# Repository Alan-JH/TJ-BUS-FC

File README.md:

# Piridium Hardware
Piridium is a CubeSat bus design inspired by TJREVERB and the concept of Pycubed. It uses a Raspberry Pi Zero as a flight computer and Iridium 9602N modem as a radio. The bus is divided into two boards, with the EPS board including six 18650 battery cells and protection and balancing circuitry, and the avionics board including everything else (flight computer, radio, telemetry ADC, inhibits and RBF, solar input charge regulators, 5V output regulator, inertial measurement unit, real time clock and CR2032 battery backup, and payload connector).

## Issues
Charge balance for current EPS prototype seems to not work, despite following datasheet recommendations exactly. Possibly a bad chip, but worth noting.

## Tech Specs
Flight Computer: Raspberry Pi Zero/Zero W

Radio: Iridium 9602N Short Burst Data

Clock: DS3232M RTC with CR2032 Battery Backup

Battery: Six 18650 Li-Ion cells (builder's discretion, recommend protected 3-4Ah) in a 3P2S configuration

Battery protection: ~7.7A overcurrent protection (charge & discharge), 4.29V/cell overcharge protection with hysteresis down to 4.05V/cell, 3V/cell overdischarge protection with hysteresis up to 3.2V/cell

Solar input: 4 input connectors feeding two regulators with 25V Max (limited by the voltage divider for telemetry) with charge cutoff at 8.27V, MPPT settable using a trim pot

Output regulation: 2 separated 5V rails up to 3A output, one for the radio, the other for the Raspberry Pi, each with latching current limiters and a watchdog timer

Payload connection: 1x SPI bus with one dedicated chip enable pin, 1x I2C bus, 1x unused configurable GPIO pin, switchable battery power (no overcurrent protection); see schematic for pinout

Telemetry: Current out and voltage in for both solar regulators, battery input voltage and current, payload battery current

Antenna connector: Standard SMA vertical

Inhibits: Two discharge inhibits (do not block charge), two RBF (one low side ground disconnect, one high side power disconnect, blocks both charge and discharge)

## Hardware notes

### Flight Computer
Raspberry Pi Zero running Raspbian OS lite. Flight software can be found here: https://github.com/Alan-JH/piridium-fsw

### Iridium Modem
Defaults to off when the bus is powered, only turns on when S_MODEM_ON_OFF is pulled high by the Raspberry Pi on GPIO pin 20. There is an LED to indicate when the modem is powered, and GPIO input for ring indicator and network availability (S_RING_INDICATOR on GPIO pin 16 and S_NET_AVAIL on GPIO pin 12, respectively). Communication with the device is done through 3.3V UART, connected to the single UART bus on the Raspberry Pi. There is also a separate connector on the board to be used with a USB to UART converter in case configuration is needed without access to the Raspberry Pi. Due to its strict power requirements the modem can only be powered with the avionics board's 5V regulators, and not through the extra port. All UART connections driven by the Pi run through a 74HC126 buffer to the modem, to prevent latchup conditions if the modem is powered off. A separate patch antenna is required, and can connect with the SMA connector on the board.

### Power Input
There are two LT3652 MPPT tracking charge regulators on the board, each with two input connectors in parallel. The intent is for two solar panels on opposite sides of the CubeSat to be connected to the input of the same regulator, since one will not be producing power while the other is. Input voltage can range up to 25V, and the maximum power point can be set using the trim potentiometer on each regulator. I recommend doing this by connecting a power supply to the input connector, setting its voltage to the desired maximum power point voltage (Vmpp) and adjusting the trim pot until the voltage at the Vmpp test point is 2.7V. The regulators each output up to 2A, and cut off charge at 8.27V float and 0.2A termination. 

### 5V Regulator
There is one TPS54394RSAR regulator on board which outputs two isolated 3A buses, which are configured to 5V. One (labelled 5VP in the schematic) feeds the radio and must not be shared with anything else. The other (labelled 5V in the schematic) feeds the RPi and may be shared, although there is no connector native to the board to do this (and it isn't recommended to share it anyways, as the RPi is an important component). Each rail has its own 5V latching current limiter that disconnects its respective voltage bus in case of an short circuit or overcurrent event on the bus. The current limiter resets after approximately 5 seconds (timed by a simple RC circuit) to check if the overcurrent state has been removed. 

### Watchdog Timer
There is a MAX6369 watchdog timer connected to the enable pin of the 5V regulator, set to reset both 5V buses if a watchdog reset signal is not received for 60 seconds. This watchdog timer is enabled by placing (or soldering) a jumper on the WDT_EN jumper, otherwise it will be disconnected from the enable pin and cannot reset power. The watchdog timer can be disabled for testing but should be enabled for flight as it reboots the system in case of a software crash. The flight software must pulse the watchdog reset pin at least once every 60 seconds if the jumper is in place (including within 60 seconds after starting to boot).

### Telemetry
One MCP3208 ADC provides voltage and current readouts, along with a MAX6035 3V reference. Telemetry readouts include Solar Regulator A Output Current (CH0) and Input Voltage (CH1), Solar Regulator B Output Current (CH2) and Input Voltage (CH3), Battery Voltage (CH4), Battery Output Current (CH5, does not read charging current, only discharging current. Includes payload current), Payload Current draw (CH6). The ADC is on CE0 of the Raspberry Pi. Each telemetry readout has a multiplier which can be found in the flight software example or by doing the math yourself :)

### Real Time Clock
A DS3232M RTC provides an uninterrupted time reading with a CR2032 battery backup. This is located on the I2C1 bus and the Raspberry Pi can be configured to use this RTC for its operating system time. 

### Inertial Measurement Unit
An Adafruit BNO055 may be placed on the board. Honestly, this doesn't really have much use though, as calibration is impossible without moving the board around yourself and gets reset with power cycles.

### Inhibits & RBF
Two inhibits and two RBF pins are available. The two inhibits are placed after the charge output but before the battery output bus on the board, so when enabled they block discharging but not charging. One RBF pin is on the high side between the EPS input terminal and everything else on the board, and the other is on the low side. Both will block discharging and charging when enabled. The inhibit connector is an 8 pin header on the bottom of the board labelled on the silkscreen. Connecting the H and L pins enable the inhibit/RBF, blocking current flow. These should be connected to separation switches on the frame that are closed when depressed. Be careful not to connect the H and L pins of different inhibit/RBFs (e.g. connecting pins 2 and 3).

### Battery protections and balancing
A BQ29209 provides resistive charge balancing and an R5460N212AF provides pack level overcurrent, overvoltage, and undervoltage protections. Due to the 20mOhm resistor connected to the R5460N212AF, battery pack output voltage will droop significantly at higher current draws (e.g. more than a few amps). Overcurrent protection uses the Rds(on) of the two MOSFETs along with the shunt resistor to total 26mOhm, so if the MOSFETs need to be substituted, recalculate the effective series resistance again to see if the resulting OCP setpoint is acceptable. If not, adjust the shunt resistor accordingly. 

## Component selection notes
For passives and unspecified components, select automotive grade (AEC-Q100, AEC-Q101, AEC-Q200, AEC-Q300 etc.) if possible. For capacitors especially, derate voltage by about 50% (i.e. for a capacitor on a line experiencing 5V, choose a cap rated for at least 10V). Also recommend sticking to X7R dielectric and resin body or soft body if possible. For 0.1uF caps, 50V for everything is fine. For 10uF, I had to order a bunch of 25V automotive grade caps for everything and a few 50V non automotive caps specifically for the solar input. For current shunts, derate the power rating by a similar amount for thermal concerns.

For the CR2032 battery, I used a Murata CR2032W for its +125C max operating temperature. The battery holder is a LINX-HLD-001-THM. For the battery terminals, use Phoenix Contact 1985807

Shield: [![CC BY-NC-SA 4.0][cc-by-nc-sa-shield]][cc-by-nc-sa]

This work is licensed under a
[Creative Commons Attribution-NonCommercial-ShareAlike 4.0 International License][cc-by-nc-sa].

[![CC BY-NC-SA 4.0][cc-by-nc-sa-image]][cc-by-nc-sa]

[cc-by-nc-sa]: http://creativecommons.org/licenses/by-nc-sa/4.0/
[cc-by-nc-sa-image]: https://licensebuttons.net/l/by-nc-sa/4.0/88x31.png
[cc-by-nc-sa-shield]: https://img.shields.io/badge/License-CC%20BY--NC--SA%204.0-lightgrey.svg

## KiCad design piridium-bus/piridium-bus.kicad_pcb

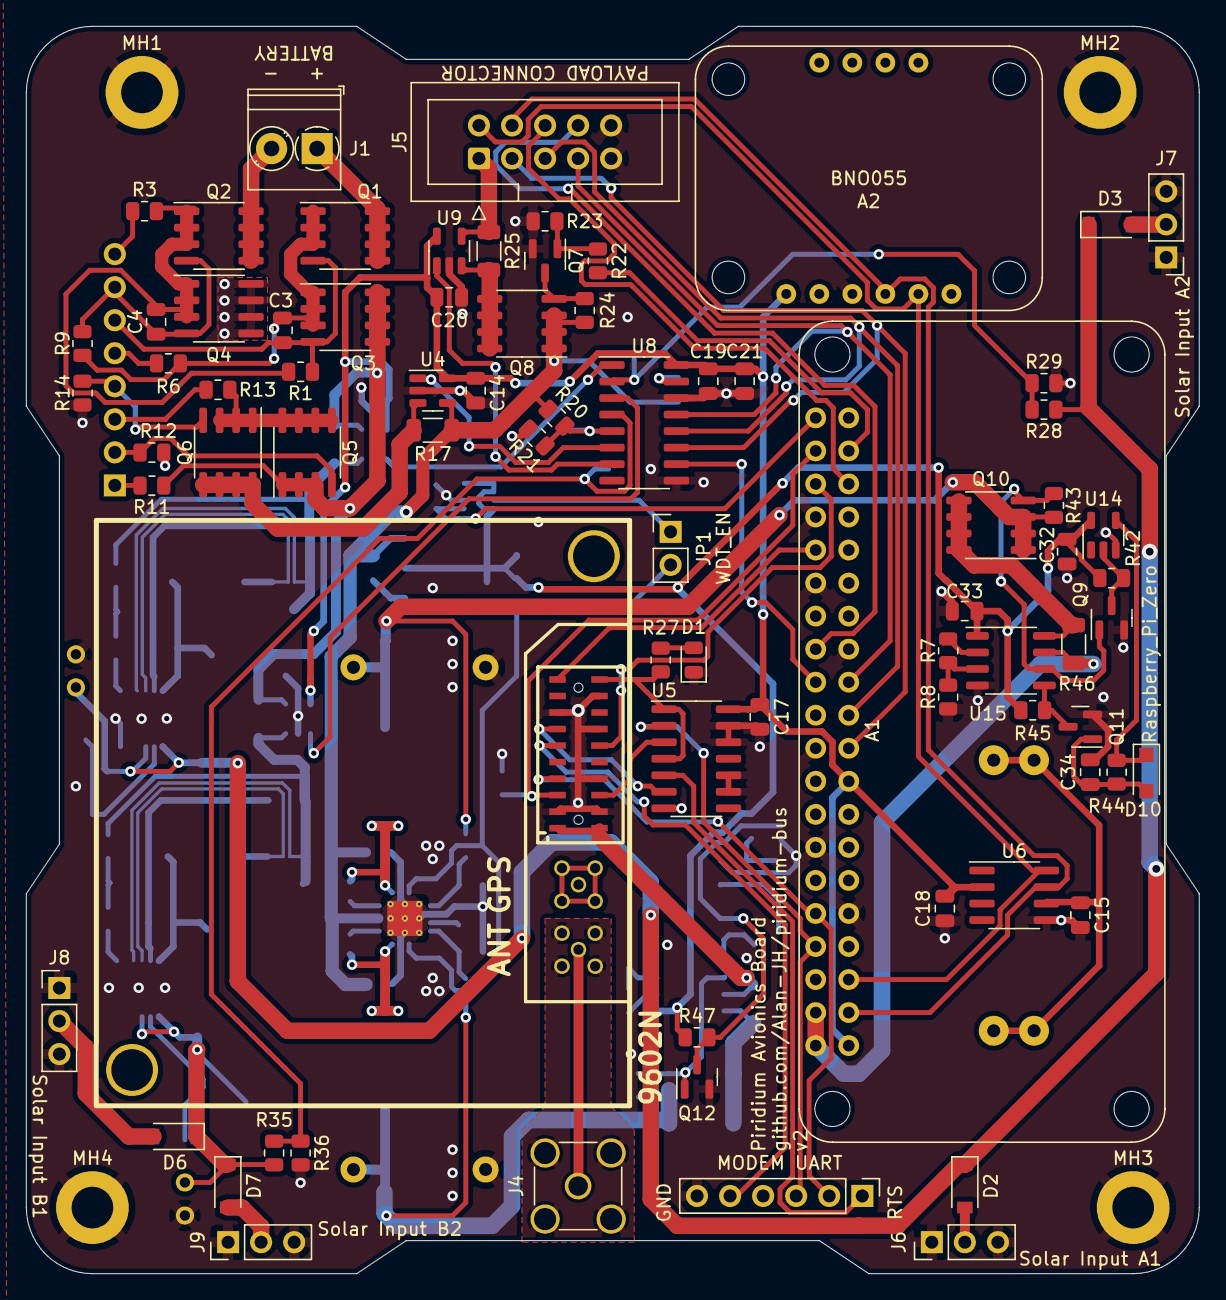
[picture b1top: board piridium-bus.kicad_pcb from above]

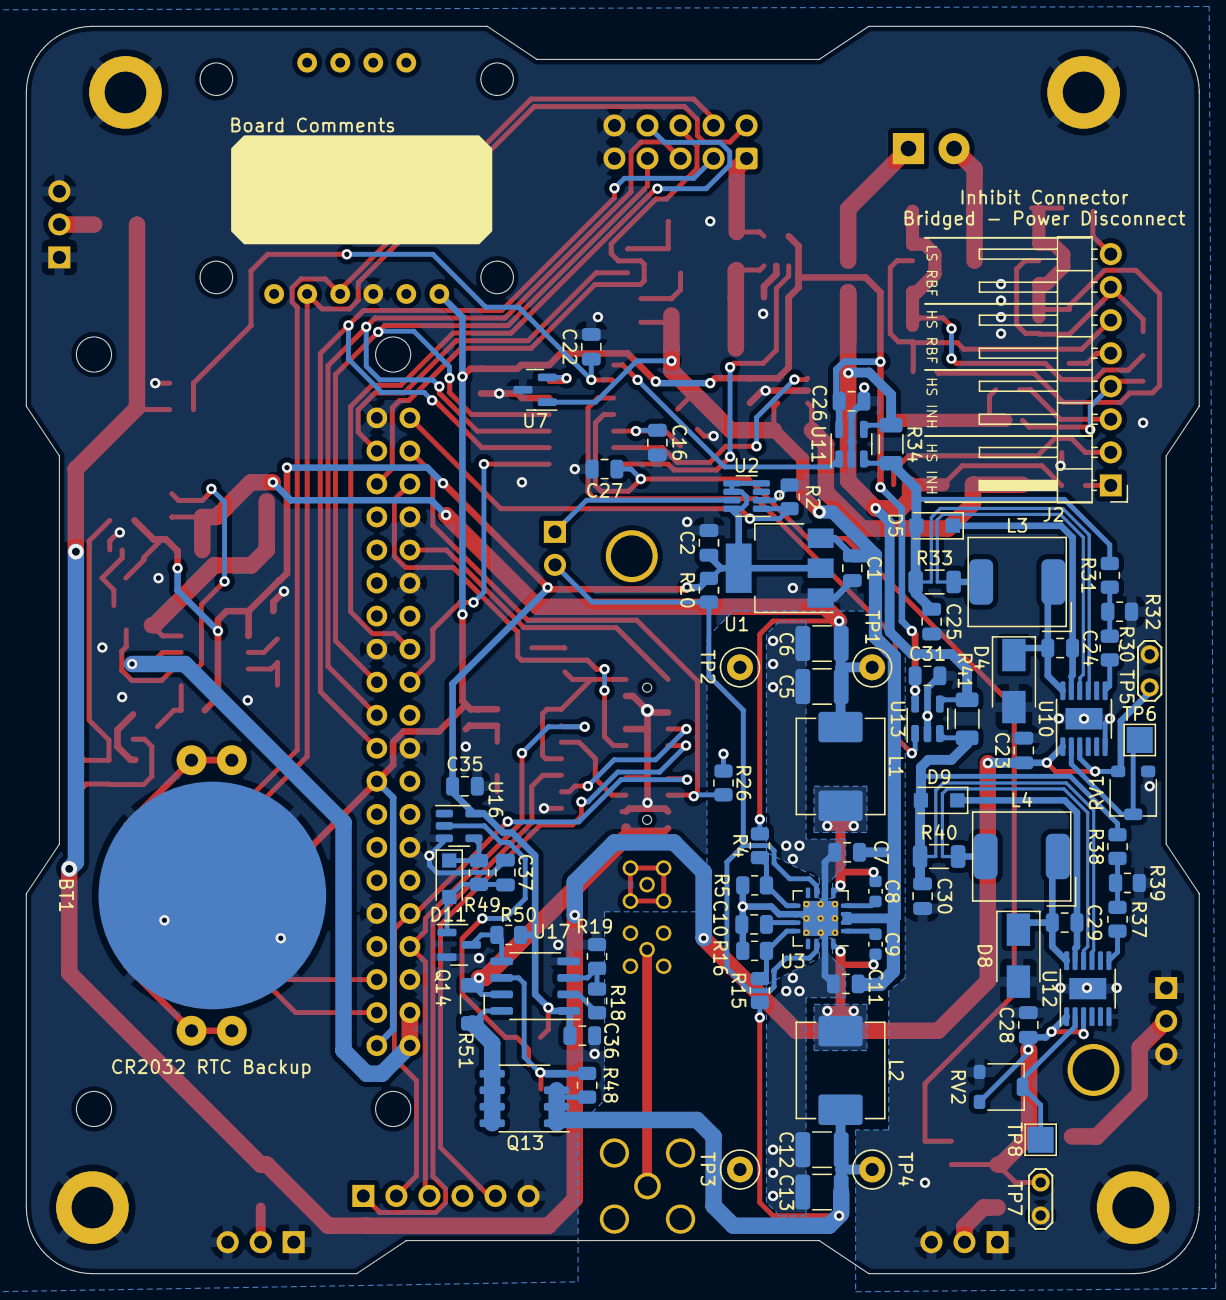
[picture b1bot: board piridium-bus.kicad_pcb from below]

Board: 4 copper layers, 90.2 x 95.9 mm, 162 parts (81 on the bottom side), 104 nets.

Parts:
A1: Raspberry_Pi_Zero; Raspberry Pi Zero
A2: BNO055
A3: 9602N; 9602
BT1: CR2032; CR2032-LINX-HLD-001-THM
C1, C7, C11, C21, C23, C25, C28, C30, C34, C37: 10uF; C_0805_2012Metric
C2, C3, C4, C14, C16, C17, C19, C20, C22, C26, C27, C31, C32, C33, C35, C36: 0.1uF; C_0805_2012Metric
C5, C6, C12, C13: 22uF; C_1210_3225Metric
C8, C9: 0.1uF; C_0603_1608Metric
C10, C15, C18, C24, C29: 1uF; C_0805_2012Metric
D1: LED; LED_0805_2012Metric
D2, D3, D6, D7: DFLS130L-7; D_SOD-123
D4, D8: CMSH3-40MA; D_SMA
D5, D9, D10, D11: RB051MM-2Y; D_SOD-123F
J1: EPS; TerminalBlock_Phoenix_PT-1,5-2-3.5-H_1x02_P3.50mm_Horizontal
J2: INHIBITS; PinHeader_1x08_P2.54mm_Horizontal
J3: MODEM UART; PinHeader_1x06_P2.54mm_Vertical
J4: ANT; SMA_Amphenol_901-144_Vertical
J5: PAYLOAD; IDC-Header_2x05_P2.54mm_Vertical
J6, J8: IN1; PinHeader_1x03_P2.54mm_Vertical
J7, J9: IN2; PinHeader_1x03_P2.54mm_Vertical
JP1: WDT_EN; PinHeader_1x02_P2.54mm_Vertical
L1, L2: 4.7uH; L_Abracon_ASPI-0630LR
L3, L4: 10uH; L_AVX_LMLP07A7
MH1, MH2, MH3, MH4: M3; MountingHole_3.2mm_M3_DIN965_Pad
Q1, Q3, Q5, Q6, Q8, Q10, Q13: DMP3015LSSQ; SOIC-8_3.9x4.9mm_P1.27mm
Q2, Q4: Si4186DY; SOIC-8_3.9x4.9mm_P1.27mm
Q7, Q9, Q11, Q12, Q14: 2N7002; SOT-23
R1, R2, R9, R10, R12, R14, R21: 100K; R_0805_2012Metric
R3, R6, R11, R13, R22: 100R; R_0805_2012Metric
R4, R15: 124K; R_0805_2012Metric
R5, R16: 22.1K; R_0805_2012Metric
R7, R18: 6K; R_0805_2012Metric
R8, R19: 4K; R_0805_2012Metric
R17, R25, R34, R41: 4m; R_1206_3216Metric
R20: 200K; R_0805_2012Metric
R23, R24, R26, R27, R29, R36, R42, R43, R45, R47, R48, R50: 10K; R_0805_2012Metric
R28, R35: 75K; R_0805_2012Metric
R30, R37: 191K; R_0805_2012Metric
R31, R38: 147K; R_0805_2012Metric
R32, R39: 97.6K; R_0805_2012Metric
R33, R40: 50m; R_1206_3216Metric
R44, R49: 510K; R_0805_2012Metric
R46, R51: 10m; R_1206_3216Metric
RV1, RV2: 100K; Bourns PVG3A
TP1: 5V; TestPoint_Loop_D2.50mm_Drill1.0mm
TP2, TP3: GND; TestPoint_Loop_D2.50mm_Drill1.0mm
TP4: 5VP; TestPoint_Loop_D2.50mm_Drill1.0mm
TP5, TP7: VIN; TestPoint_2Pads_Pitch2.54mm_Drill0.8mm
TP6, TP8: Vmpp; TestPoint_Pad_2.0x2.0mm
U1: LM1117-3.3; SOT-223-3_TabPin2
U2: MAX6369; SOT-23-8
U3: TPS54394RSAR; Texas_S-PVQFN-N16_EP2.7x2.7mm_ThermalVias
U4, U9, U11, U13: INA180A3; SOT-23-5
U5: 74HC126; SOIC-14_3.9x8.7mm_P1.27mm
U6: DS3232M; SOIC-8_3.9x4.9mm_P1.27mm
U7: MAX6035xxUR30; SOT-23
U8: MCP3208; SOIC-16_3.9x9.9mm_P1.27mm
U10, U12: LT3652EMSE; MSOP-12-1EP_3x4mm_P0.65mm_EP1.65x2.85mm
U14, U16: SN74LVC1G14DBV; SOT-23-5
U15, U17: MAX4373F; SO-8_3.9x4.9mm_P1.27mm

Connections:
+3.3V: A1.1 (3V3), A1.17 (3V3), A2.1 (VIN), C14.1, C17.1, C18.2, C19.1, C20.1, C21.1, C26.1, C31.1, U4.5 (V+), U5.14 (VCC), U6.2 (VCC), U8.16 (Vdd), U9.5 (V+), U11.5 (V+), U13.5 (V+)
+3.3VA: C2.1, C32.1, C33.1, C35.1, C36.1, R10.1, R42.1, R45.1, R47.1, R50.1, U1.2 (VO), U2.4 (SET0), U2.5 (SET1), U2.6 (SET2), U2.8 (VCC), U14.5 (VCC), U15.1 (Vcc), U16.5 (VCC), U17.1 (Vcc)
+5V: A1.2 (5V), A1.4 (5V), R46.1, U15.7 (RS-)
+5VP: A3.1 (EXT_PWR), A3.2 (EXT_PWR), R51.1, U17.7 (RS-)
+BATT: C1.1, C7.1, C11.1, Q8.1 (S), Q8.2 (S), Q8.3 (S), R17.1, R20.1, R24.1, U1.3 (VI), U3.2 (VIN2), U3.3 (VIN1), U4.4 (-), U7.1 (IN)
/5V LCL/CIN1: R7.2, R8.1, U15.3 (CIN1)
/5V LCL/OUT: R7.1, U15.2 (OUT)
/5V LCL/POWER_IN: C5.1, C6.1, L1.1, Q10.1 (S), Q10.2 (S), Q10.3 (S), R4.1, R43.1, TP1.1
/5VP LCL/CIN1: R18.2, R19.1, U17.3 (CIN1)
/5VP LCL/OUT: R18.1, U17.2 (OUT)
/5VP LCL/POWER_IN: C12.1, C13.1, L2.2, Q13.1 (S), Q13.2 (S), Q13.3 (S), R15.1, R48.1, TP4.1
/A1H: J2.5, R6.2
/A1L: C3.2, J2.6, Q1.4 (G), Q3.4 (G), R1.1
/A2H: C4.1, J2.7, Q2.4 (G), Q4.4 (G), R9.2
/A2L: J2.8, R3.1
/B1H: J2.1, R11.2
/B1L: J2.2, Q5.4 (G), R12.1
/B2H: J2.3, R13.2
/B2L: J2.4, Q6.4 (G), R14.1
/CHARGE_OUT: Q3.5 (D), Q3.6 (D), Q3.7 (D), Q3.8 (D), Q5.1 (S), Q5.2 (S), Q5.3 (S), R11.1, R34.1, R41.1, U11.4 (-), U13.4 (-)
/EN: JP1.2 (B), R10.2, U3.7 (EN1), U3.14 (EN2)
/I_OUT_A: U8.1 (CH0), U11.1
/I_OUT_B: U8.3 (CH2), U13.1
/PAYLOAD_PWR: J5.1, R25.1, U9.4 (-)
/SUP_OUT: A3.20 (SUPPLY_OUT), R27.1, U5.1, U5.4
/V_IN_A: C22.1, R28.2, R29.1, U8.2 (CH1)
/V_IN_B: C27.1, R35.2, R36.1, U8.4 (CH3)
ADC_CS: A1.24 (8(CE0)), U8.10 (~CS/SHDN)
GND: A1.6 (GND), A1.9 (GND), A1.14 (GND), A1.20 (GND), A1.25 (GND), A1.30 (GND), A1.34 (GND), A1.39 (GND), A2.3 (GND), A3.3 (EXT_GND), A3.4 (EXT_GND), A3.8 (SIG_GND), A3.14 (DF_DTR), A3.15 (SIG_GND), A3.18 (SIG_GND), BT1.2 (-), C1.2, C2.2, C5.2, C6.2, C7.2, C10.2, C11.2, C12.2, C13.2, C14.2, C15.2, C16.2, C17.2, C18.1, C19.2, C20.2, C21.2, C22.2, C23.2, C25.2, C26.2, C27.2, C28.2, C30.2, C31.2, C32.2, C33.2, C34.2, C35.2, C36.2, C37.2, D1.1 (K), D4.2 (A), D8.2 (A), J3.6, J5.9, J5.10, J6.1, J6.3, J7.1, J7.3, J8.1, J8.3, J9.1, J9.3, MH1.1, MH2.1, MH3.1, MH4.1, Q4.5 (D), Q4.6 (D), Q4.7 (D), Q4.8 (D), Q7.2 (S), Q9.2 (S), Q11.2 (S), Q12.2 (S), Q14.2 (S), R2.2, R5.2, R8.2, R12.2, R14.2, R16.2, R19.2, R21.2, R23.2, R26.2, R29.2, R32.1, R36.2, R39.1, RV1.3, RV2.3, TP2.1, TP3.1, TP5.1, TP7.1, U1.1 (GND), U2.2 (GND), U3.6 (PGND1), U3.10 (GND), U3.15 (PGND2), U3.17 (PADGND), U4.2 (GND), U5.7 (GND), U5.9, U5.10, U5.12, U5.13, U6.5 (GND), U7.3 (GND), U8.9 (DGND), U8.14 (AGND), U9.2 (GND), U10.6 (TIMER), U10.13 (GND), U11.2 (GND), U12.6 (TIMER), U12.13 (GND), U13.2 (GND), U14.3 (GND), U15.4 (GND), U16.3 (GND), U17.4 (GND)
GNDS: A3.22 (RF_GND), J4.2 (Ext)
GPIO19: A1.35 (19(PWM1)), J5.6
I2C_SCL: A1.5 (3(SCL1)), A2.5 (SCL), J5.2, U6.8 (SCL)
I2C_SDA: A1.3 (2(SDA1)), A2.4 (SDA), J5.4, U6.7 (SDA)
unnamed: A3.6 (DF_S_TX), U5.3
unnamed: A3.13 (DF_RTS), U5.6
unnamed: A3.21 (RF_ANT), J4.1 (In)
unnamed: BT1.1 (+), C15.1, U6.6 (VBAT)
unnamed: C3.1, Q1.1 (S), Q1.2 (S), Q1.3 (S), Q3.1 (S), Q3.2 (S), Q3.3 (S), R6.1, R9.1
unnamed: C4.2, Q2.1 (S), Q2.2 (S), Q2.3 (S), Q4.1 (S), Q4.2 (S), Q4.3 (S), R1.2, R3.2
unnamed: C8.1, U3.4 (VBST1)
unnamed: C8.2, L1.2, U3.5 (SW1)
unnamed: C9.1, U3.1 (VBST2)
unnamed: C9.2, L2.1, U3.16 (SW2)
unnamed: C10.1, U3.11 (VREG5)
unnamed: C23.1, D2.1 (K), D3.1 (K), R28.1, RV1.1, TP5.2, U10.1 (VIN), U10.3 (~SHDN)
unnamed: C24.1, D4.1 (K), L3.1, U10.12 (SW)
unnamed: C24.2, D5.1 (K), U10.11 (BOOST)
unnamed: C25.1, D5.2 (A), R31.2, R33.1, R34.2, U10.9 (BAT), U11.3 (+)
unnamed: C28.1, D6.1 (K), D7.1 (K), R35.1, RV2.1, TP7.2, U12.1 (VIN), U12.3 (~SHDN)
unnamed: C29.1, D8.1 (K), L4.1, U12.12 (SW)
unnamed: C29.2, D9.1 (K), U12.11 (BOOST)
unnamed: C30.1, D9.2 (A), R38.2, R40.1, R41.2, U12.9 (BAT), U13.3 (+)
unnamed: C34.1, D10.2 (A), Q11.1 (G), R44.2
unnamed: C37.1, D11.2 (A), Q14.1 (G), R49.2
unnamed: D1.2 (A), R27.2
unnamed: D2.2 (A), J6.2
unnamed: D3.2 (A), J7.2
unnamed: D6.2 (A), J8.2
unnamed: D7.2 (A), J9.2
unnamed: D10.1 (K), R44.1, U14.4
unnamed: D11.1 (K), R49.1, U16.4
unnamed: J1.1, Q1.5 (D), Q1.6 (D), Q1.7 (D), Q1.8 (D)
unnamed: J1.2, Q2.5 (D), Q2.6 (D), Q2.7 (D), Q2.8 (D)
unnamed: JP1.1 (A), U2.7 (~WDO)
unnamed: L3.2, R33.2, U10.10 (SENSE)
unnamed: L4.2, R40.2, U12.10 (SENSE)
unnamed: Q5.5 (D), Q5.6 (D), Q5.7 (D), Q5.8 (D), Q6.1 (S), Q6.2 (S), Q6.3 (S), R13.1
unnamed: Q6.5 (D), Q6.6 (D), Q6.7 (D), Q6.8 (D), R17.2, U4.3 (+)
unnamed: Q7.1 (G), R22.1, R23.1
unnamed: Q7.3 (D), Q8.4 (G), R24.2
unnamed: Q8.5 (D), Q8.6 (D), Q8.7 (D), Q8.8 (D), R25.2, U9.3 (+)
unnamed: Q9.3 (D), R42.2, U14.2
unnamed: Q9.1 (G), Q10.4 (G), R43.2, U15.6 (COUT1)
unnamed: Q10.5 (D), Q10.6 (D), Q10.7 (D), Q10.8 (D), R46.2, U15.8 (RS+)
unnamed: Q11.3 (D), R45.2, U15.5 (~RESET)
unnamed: Q12.1 (G), Q13.4 (G), R48.2, U17.6 (COUT1)
unnamed: Q12.3 (D), R47.2, U16.2
unnamed: Q13.5 (D), Q13.6 (D), Q13.7 (D), Q13.8 (D), R51.2, U17.8 (RS+)
unnamed: Q14.3 (D), R50.2, U17.5 (~RESET)
unnamed: R4.2, R5.1, U3.9 (VFB1)
unnamed: R15.2, R16.1, U3.12 (VFB2)
unnamed: R30.1, R31.1, R32.2
unnamed: R30.2, U10.7 (VFB)
unnamed: R37.1, R38.1, R39.2
unnamed: R37.2, U12.7 (VFB)
unnamed: RV1.2, TP6.1, U10.2 (VIN_REG)
unnamed: RV2.2, TP8.1, U12.2 (VIN_REG)
unnamed: U7.2 (OUT), U8.15 (Vref)
SPI_CE1: A1.26 (7(CE1)), J5.8
SPI_MISO: A1.21 (9(MISO)), J5.5, U8.12 (Dout)
SPI_MOSI: A1.19 (10(MOSI)), J5.3, U8.11 (Din)
SPI_SCK: A1.23 (11(SCK)), J5.7, U8.13 (CLK)
S_HANDSHAKE: A1.40 (21), R2.1, U2.1 (WDI)
S_MODEM_ON_OFF: A1.38 (20), A3.5 (ON/OFF), R26.1
S_NET_AVAIL: A1.32 (12(PWM0)), A3.19 (NET_AVAIL)
S_PAYLOAD_PWR: A1.37 (26), R22.2
S_RING_INDICATOR: A1.36 (16), A3.12 (DF_RI)
TELEM_IBAT: U4.1, U8.6 (CH5)
TELEM_IPAYLOAD: U8.7 (CH6), U9.1
TELEM_VBATV: C16.1, R20.2, R21.1, U8.5 (CH4)
UART_CTS: A3.11 (DF_CTS), J3.5
UART_RTS: J3.1, U5.5
UART_RX: A1.10 (15(RxD)), A3.7 (DF_S_RX), J3.2
UART_TX: A1.8 (14(TxD)), J3.3, U5.2

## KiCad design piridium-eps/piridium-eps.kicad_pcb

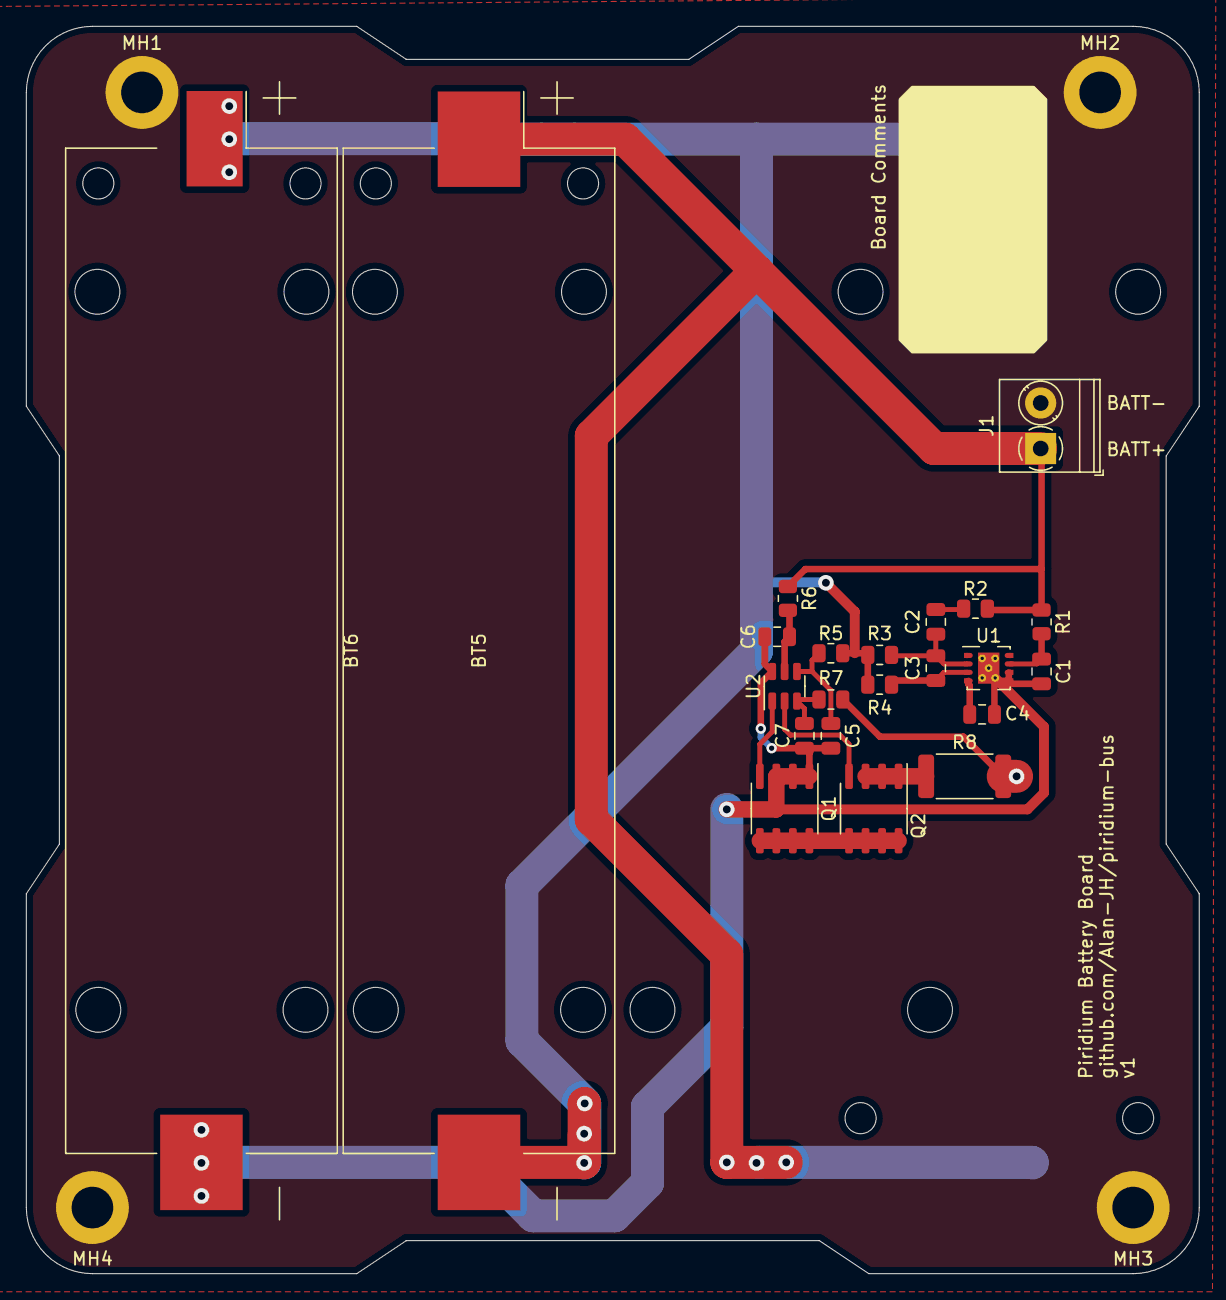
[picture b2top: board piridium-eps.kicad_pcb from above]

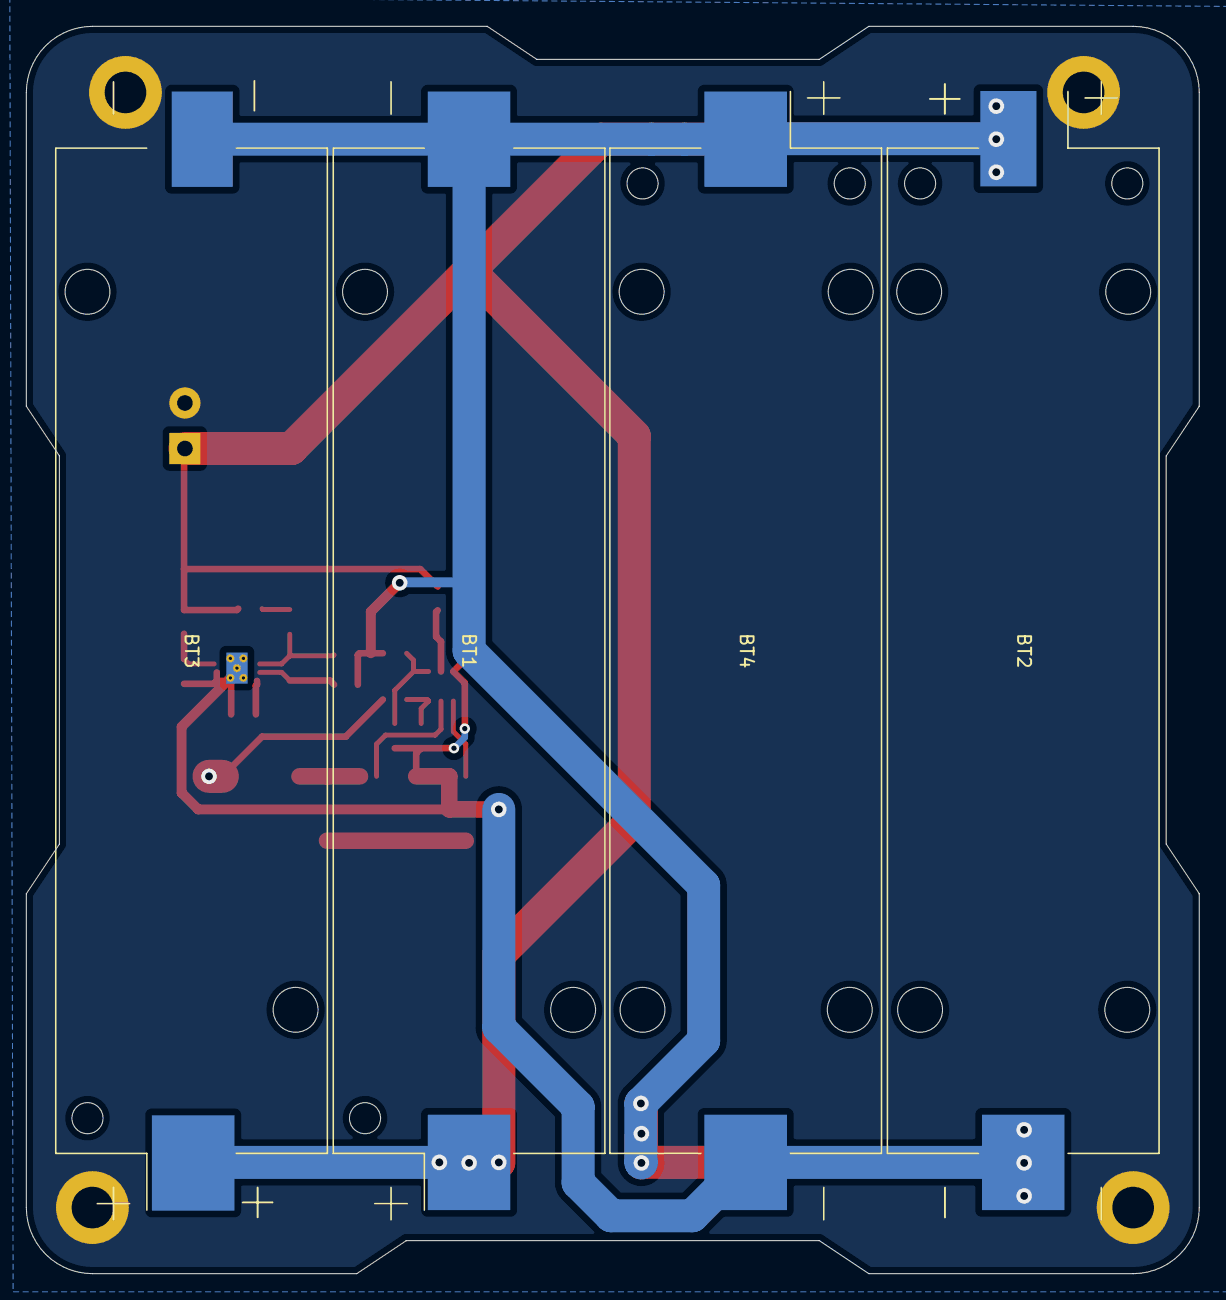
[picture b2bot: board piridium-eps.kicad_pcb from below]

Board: 2 copper layers, 90.2 x 95.9 mm, 30 parts (4 on the bottom side), 16 nets.

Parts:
BT1, BT4, BT5: 18650; BatteryHolder_Keystone_1042_1x18650
BT2: 18650; Keystone_1042_1x18650_Shortpad
BT3: 18650; Keystone_1042_1x18650_Shortpad2
BT6: 18650; Keystone_1042_1x18650_Shortpad3
C1, C2, C3, C4, C5, C6, C7: 0.1uF; C_0805_2012Metric
J1: EPS; TerminalBlock_Phoenix_PT-1,5-2-3.5-H_1x02_P3.50mm_Horizontal
MH1, MH2, MH3, MH4: M3; MountingHole_3.2mm_M3_DIN965_Pad
Q1, Q2: Si4186DY; SOIC-8_3.9x4.9mm_P1.27mm
R1, R4: 100R; R_0805_2012Metric
R2: 160R; R_0805_2012Metric
R3, R5, R6: 261R; R_0805_2012Metric
R7: 1K; R_0805_2012Metric
R8: 20m; R_2512_6332Metric
U1: BQ29209; Texas_S-PVSON-N8_ThermalVias
U2: R5460N212AF; SOT-23-6

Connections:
+BATT: BT1.1 (+), BT3.1 (+), BT5.1 (+), J1.1, R1.1, R2.1, R6.1
-BATT: BT2.2 (-), BT4.2 (-), BT6.2 (-), C1.2, C4.2, C5.2, C6.2, C7.1, Q1.1 (S), Q1.2 (S), Q1.3 (S), U1.5 (GND), U1.6 (~{CB_EN), U1.9 (PGND), U2.6 (Vss)
GND: J1.2, MH1.1, MH2.1, MH3.1, MH4.1, R7.2, R8.2
unnamed: BT1.2 (-), BT2.1 (+), BT3.2 (-), BT4.1 (+), BT5.2 (-), BT6.1 (+), R3.1, R4.1, R5.1
unnamed: C1.1, R1.2, U1.7 (VDD)
unnamed: C2.1, R2.2
unnamed: C2.2, C3.1, R3.2, U1.2 (VC1)
unnamed: C3.2, R4.2, U1.3 (VC1_CB)
unnamed: C4.1, U1.4 (CD)
unnamed: C5.1, R5.2, U2.4 (Vc)
unnamed: C6.1, R6.2, U2.5 (Vdd)
unnamed: C7.2, R7.1, U2.3 (V-)
unnamed: Q1.4 (G), U2.1 (Dout)
unnamed: Q1.5 (D), Q1.6 (D), Q1.7 (D), Q1.8 (D), Q2.5 (D), Q2.6 (D), Q2.7 (D), Q2.8 (D)
unnamed: Q2.1 (S), Q2.2 (S), Q2.3 (S), R8.1
unnamed: Q2.4 (G), U2.2 (Cout)

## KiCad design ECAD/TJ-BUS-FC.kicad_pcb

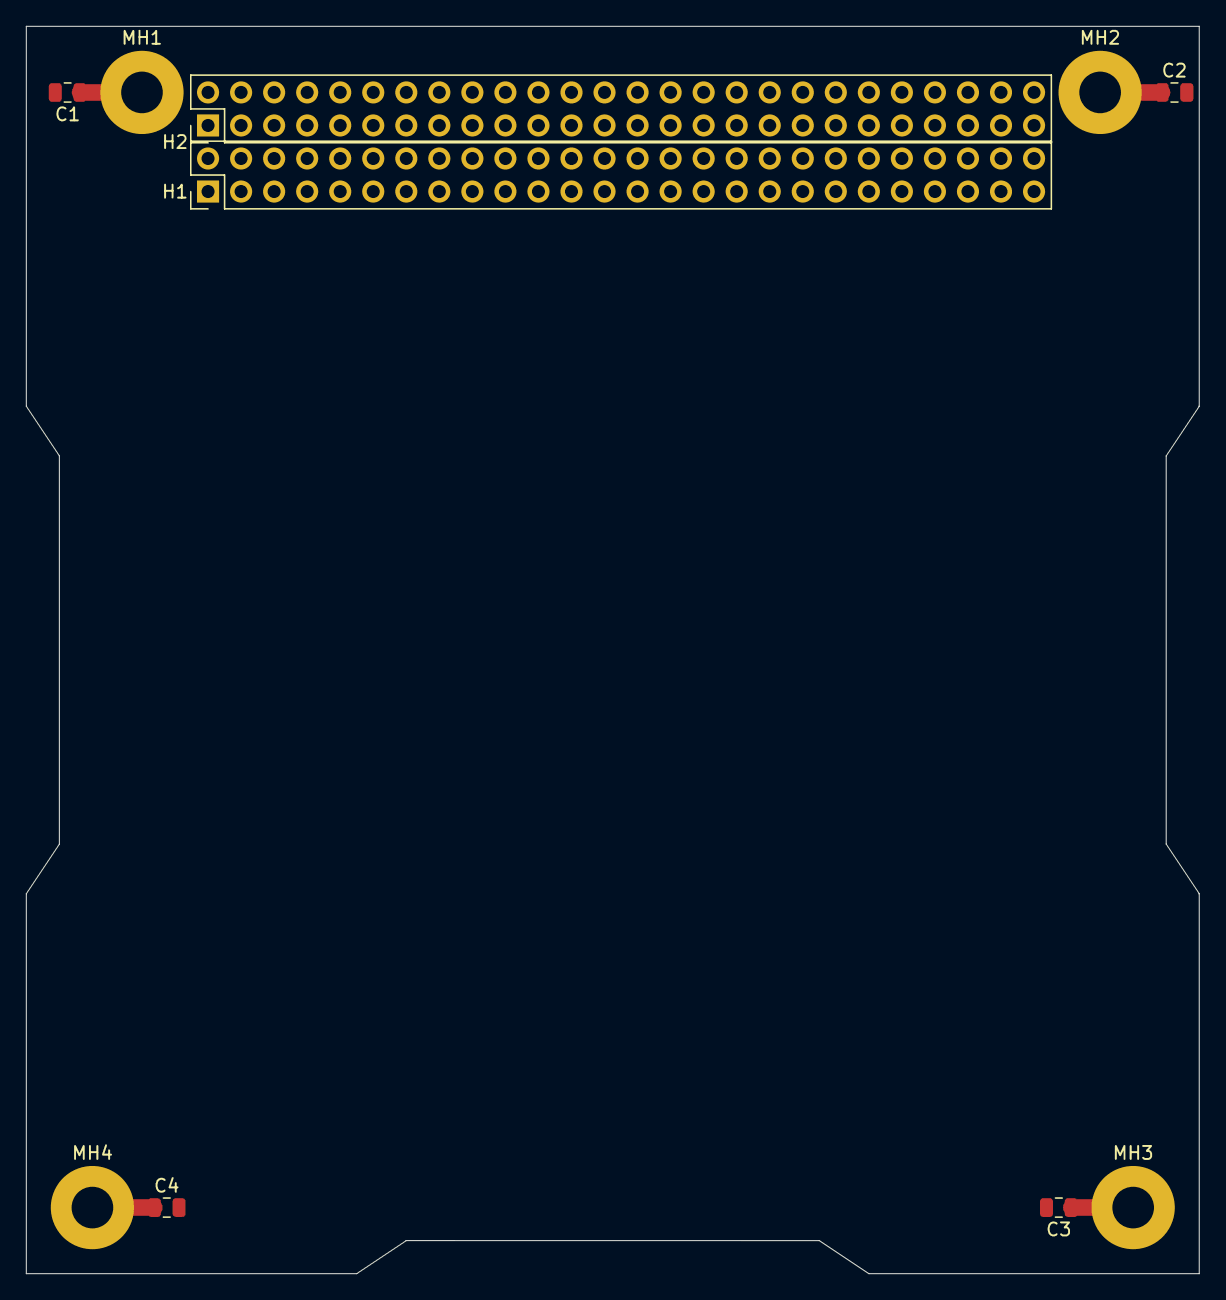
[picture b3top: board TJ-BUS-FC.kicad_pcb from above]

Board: 2 copper layers, 90.2 x 95.9 mm, 10 parts (0 on the bottom side), 6 nets.

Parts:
C1, C2, C3, C4: 0.1uF; C_0805_2012Metric
H1, H2: Stack Header; PinHeader_2x26_P2.54mm_Vertical
MH1, MH2, MH3, MH4: M3; MountingHole_3.2mm_M3_Pad

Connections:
BCR_OUT: H2.41, H2.43, H2.44
GND: C1.2, C2.2, C3.2, C4.2
unnamed: C1.1, MH1.1
unnamed: C2.1, MH2.1
unnamed: C3.1, MH3.1
unnamed: C4.1, MH4.1

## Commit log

2022-03-28 add iridium-stack components
2022-03-28 teensy lib
2022-03-28 bno055
2022-03-29 gpio
2022-04-02 minor fix
2022-05-01 fram module and preliminary linking
2022-05-02 remove 5VIN
2022-05-02 changed fram chip
2022-05-02 set low activated pins to high
2022-05-02 minor nitpicks
2022-05-02 add footprints and update iridium section
2022-10-18 fresh start
2022-10-20 sch milestone
2022-10-25 finish up piridium-bus schematic, cleanup footprint associations and symbols, start battery
2022-10-25 transfer some TJ-EPS circuitry to eps
2022-10-31 some work on routing
2022-11-01 routing work on bus
2022-11-02 update routing
2022-11-05 add inhibits, telemetry, and solar to bus
2022-11-06 fix bus board messup, remove redundant components from eps
2022-11-10 ngl not sure what I did here
2022-11-10 routing work
2022-11-16 route inhibits and some other power path stuff
2022-11-17 route data lines, begin to route MPPT circuitry
2022-11-17 route solar
2022-11-17 finish routing
2022-11-17 cleanup silkscreen
2022-11-17 copy pycubed battery
2022-11-21 add max4373f
2022-11-28 prototype timing circuit for LCL reset
2022-11-28 move LCLs to hierarchical sheets
2022-11-29 add R5460 and small bom edits
2022-11-29 battery sch finish
2022-12-01 route LCLs
2022-12-05 license
2022-12-13 finish battery
2022-12-15 switch battery to 2 layer
2022-12-19 correct max4373 implementation, #5 and #4
2022-12-22 move adc to hardware cs pin, start routing updated LCLs
2022-12-23 finish v2 (#6 and finish #5/#4)
2022-12-28 mcp3208 constant reference
2022-12-28 gerber re export
2022-12-29 pull down on/off instead of up
2022-12-29 final trace edits
2023-01-11 fix max6035 dropout
2023-09-11 Fix some README wording
